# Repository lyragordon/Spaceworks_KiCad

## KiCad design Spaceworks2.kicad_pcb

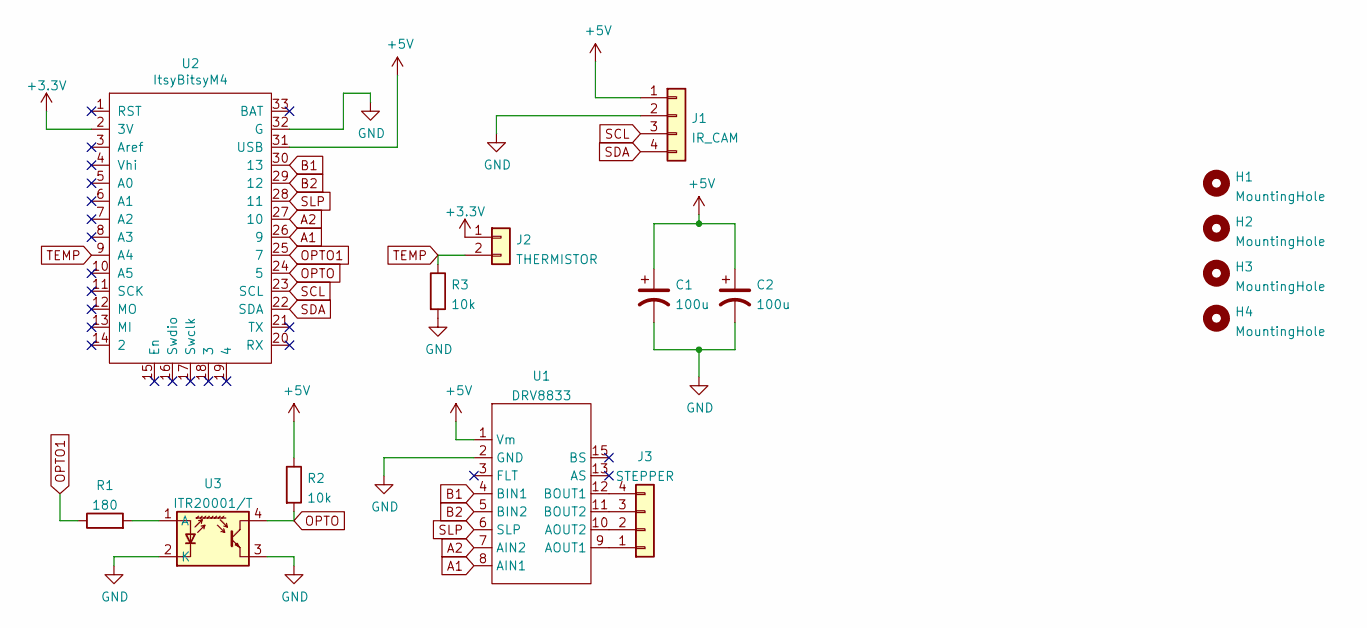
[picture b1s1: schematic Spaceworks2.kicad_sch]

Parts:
C1, C2: 100u; CP_Radial_D5.0mm_P2.50mm
H1, H2, H3, H4: MountingHole; MountingHole_2.1mm
J1: IR_CAM; JST_PH_B4B-PH-SM4-TB_1x04-1MP_P2.00mm_Vertical
J2: THERMISTOR; JST_PH_B2B-PH-SM4-TB_1x02-1MP_P2.00mm_Vertical
J3: STEPPER; JST_PH_B4B-PH-SM4-TB_1x04-1MP_P2.00mm_Vertical
R1: 180; R_Axial_DIN0207_L6.3mm_D2.5mm_P7.62mm_Horizontal
R2, R3: 10k; R_Axial_DIN0207_L6.3mm_D2.5mm_P7.62mm_Horizontal
U1: DRV8833
U2: ItsyBitsyM4; Adafruit_ItsyBitsy_M4
U3: ITR20001/T; ITR20001T

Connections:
+3V3: J2.1, U2.2 (3V)
+5V: C1.1, C2.1, J1.1, R2.1, U1.1 (Vm), U2.31 (USB)
A1: U1.8 (AIN1), U2.26 (9)
A2: U1.7 (AIN2), U2.27 (10)
B1: U1.4 (BIN1), U2.30 (13)
B2: U1.5 (BIN2), U2.29 (12)
GND: C1.2, C2.2, J1.2, R3.2, U1.2 (GND), U2.32 (G), U3.2 (K), U3.3
unnamed: J3.1, U1.9 (AOUT1)
unnamed: J3.2, U1.10 (AOUT2)
unnamed: J3.3, U1.11 (BOUT2)
unnamed: J3.4, U1.12 (BOUT1)
unnamed: R1.2, U3.1 (A)
OPTO: R2.2, U2.24 (5), U3.4
OPTO1: R1.1, U2.25 (7)
SCL: J1.3, U2.23 (SCL)
SDA: J1.4, U2.22 (SDA)
SLP: U1.6 (SLP), U2.28 (11)
TEMP: J2.2, R3.1, U2.9 (A4)

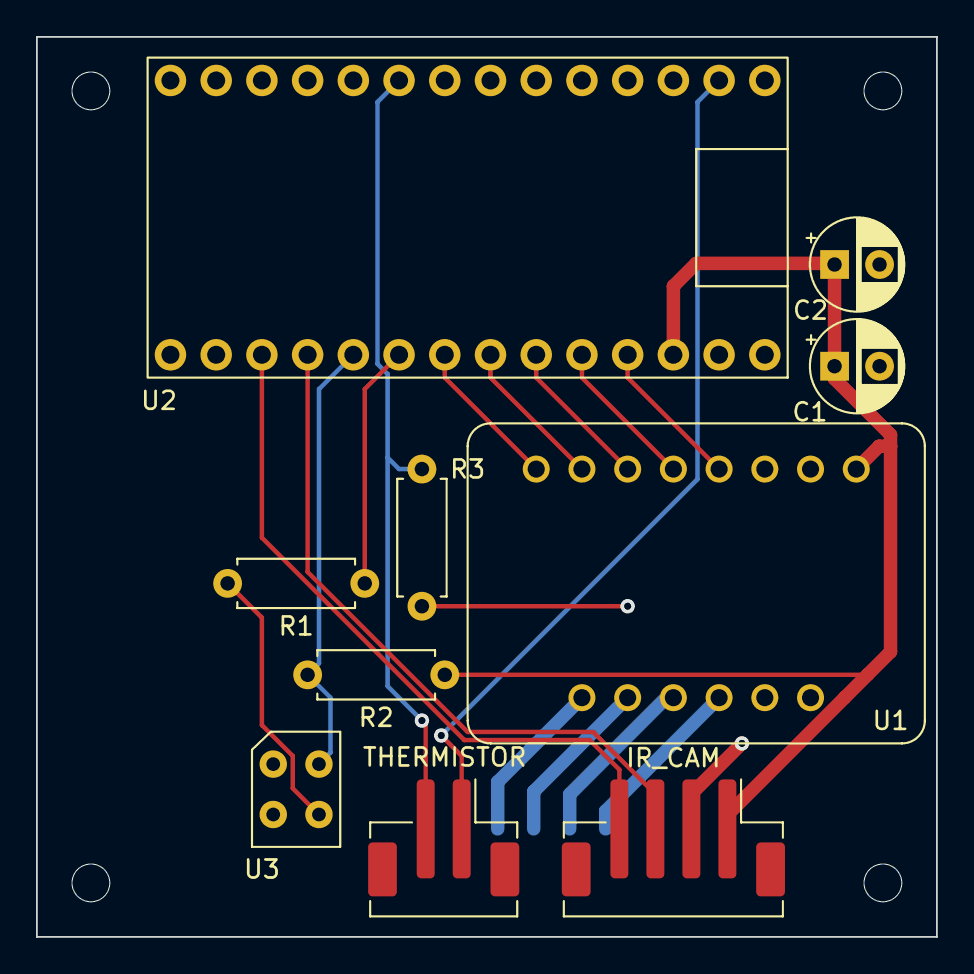
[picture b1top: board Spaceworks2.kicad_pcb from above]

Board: 2 copper layers, 50.0 x 50.0 mm, 15 parts (1 on the bottom side), 18 nets.

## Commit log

2022-03-10 Initial release
2022-03-13 Added schematic png
2022-03-13 created readme
2022-03-13 Added schem to readme
2022-03-13 Changed schematic png
2022-04-11 Fixed OPTO conn, Thermistor voltage divider resistor
